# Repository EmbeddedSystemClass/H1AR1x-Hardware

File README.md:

# H1AR1x-Hardware
Hexabitz USB-B-to-UART Converter Module Hardware Design

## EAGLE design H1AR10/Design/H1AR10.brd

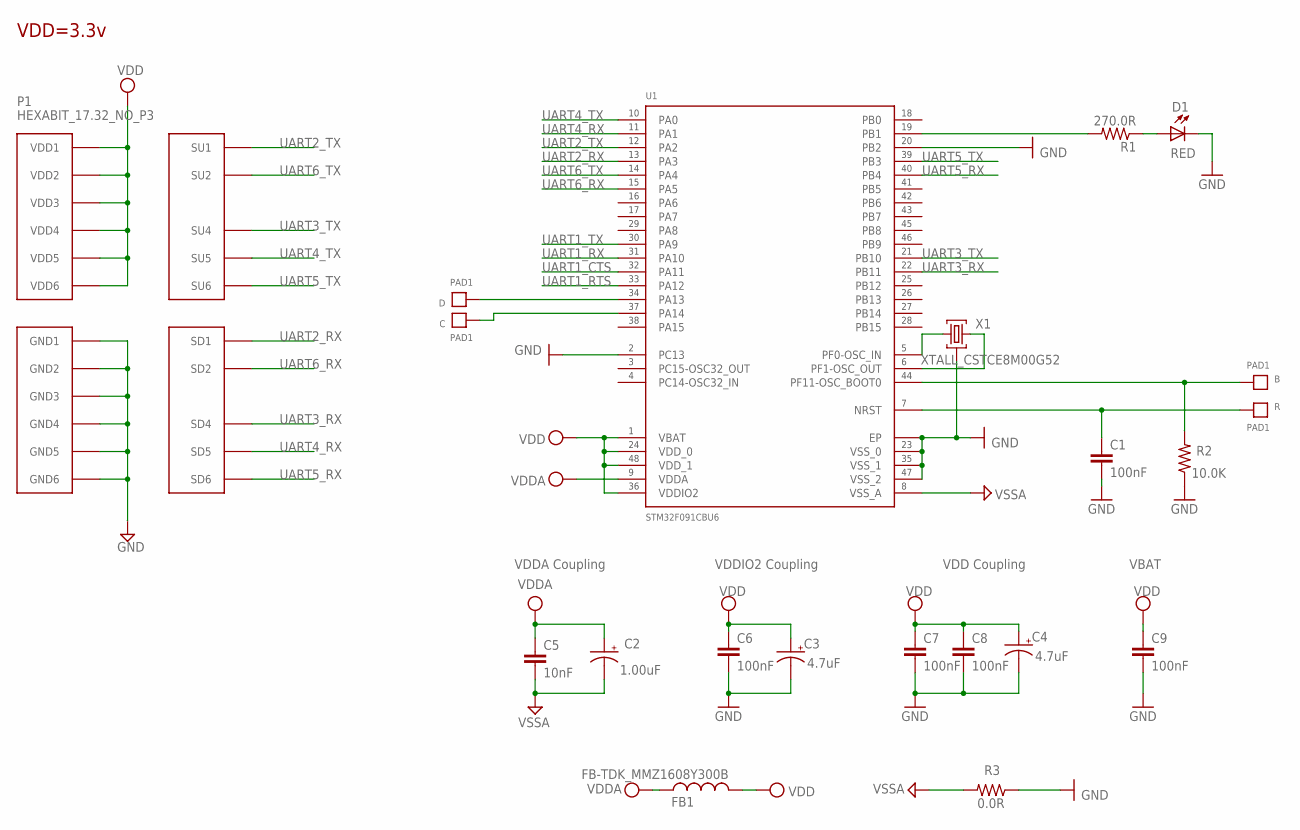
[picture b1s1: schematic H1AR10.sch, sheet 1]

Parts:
B: PAD1
C: PAD1
C1, C6, C7, C8, C9: 100nF; C-0603; TOLERANCE 10%; VOLTAGE_RATING 16V; MPN 0603YC104K4T2A
C2: 1.00uF; C-0805-POL; TOLERANCE 20%; VOLTAGE_RATING 16V; MPN TAJR105M016RNJ
C3, C4: 4.7uF; C-0805-POL; TOLERANCE 20%; VOLTAGE_RATING 10V; MPN 10TPU4R7MSI
C5: 10nF; C-0603; TOLERANCE 10%; VOLTAGE_RATING 16V; MPN 0603YC103KAT4A
D: PAD1
D1: RED; VLMS1300-GS08; MPN VLMS1300-GS08
FB1: FB-TDK_MMZ1608Y300B; MPN MMZ1608Y300B
P1: HEXABIT_17.32_NO_P3
R: PAD1
R1: 270.0R; R-0603; TOLERANCE 5%; MPN ERJ-3GEYJ271V
R2: 10.0K; R-0603; TOLERANCE 5%; MPN CRCW060310K0JNEB
R3: 0.0R; R-0603; MPN CRCW06030000Z0EAHP
U1: STM32F091CBU6
X1: XTALL_CSTCE8M00G52

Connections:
B1: B.P$1, B.P$2, R2.2, U1.P$44 (PF11-OSC_BOOT0)
GND: C1.2, C3.2 (-), C4.2 (-), C6.2, C7.2, C8.2, C9.2, D1.C, P1.PAD_PD7 (GND1), P1.PAD_PD8 (GND2), P1.PAD_PD9 (GND3), P1.PAD_PD10 (GND4), P1.PAD_PD11 (GND5), P1.PAD_PD12 (GND6), R2.1, R3.1, U1.EP, U1.P$2 (PC13), U1.P$20 (PB2), U1.P$23 (VSS_0), U1.P$35 (VSS_1), U1.P$47 (VSS_2), X1.P$2 (2); also elsewhere on the board
unnamed: U1.P$5 (PF0-OSC_IN), X1.P$1 (1)
unnamed: U1.P$6 (PF1-OSC_OUT), X1.P$3 (3)
unnamed: D.P$1, D.P$2, U1.P$34 (PA13)
unnamed: C.P$1, C.P$2, U1.P$37 (PA14)
unnamed: D1.A, R1.1
unnamed: R1.2, U1.P$19 (PB1)
R1: C1.1, R.P$1, R.P$2, U1.P$7 (NRST)
UART1_CTS: U1.P$32 (PA11); also elsewhere on the board
UART1_RTS: U1.P$33 (PA12); also elsewhere on the board
UART1_RX: U1.P$31 (PA10); also elsewhere on the board
UART1_TX: U1.P$30 (PA9); also elsewhere on the board
UART2_RX: P1.PAD_PD1 (SD1), U1.P$13 (PA3)
UART2_TX: P1.PAD_PU1 (SU1), U1.P$12 (PA2)
UART3_RX: P1.PAD_PD4 (SD4), U1.P$22 (PB11)
UART3_TX: P1.PAD_PU4 (SU4), U1.P$21 (PB10)
UART4_RX: P1.PAD_PD5 (SD5), U1.P$11 (PA1)
UART4_TX: P1.PAD_PU5 (SU5), U1.P$10 (PA0)
UART5_RX: P1.PAD_PD6 (SD6), U1.P$40 (PB4)
UART5_TX: P1.PAD_PU6 (SU6), U1.P$39 (PB3)
UART6_RX: P1.PAD_PD2 (SD2), U1.P$15 (PA5)
UART6_TX: P1.PAD_PU2 (SU2), U1.P$14 (PA4)
VDD: C3.1 (+), C4.1 (+), C6.1, C7.1, C8.1, C9.1, FB1.2, P1.PAD_PU7 (VDD1), P1.PAD_PU8 (VDD2), P1.PAD_PU9 (VDD3), P1.PAD_PU10 (VDD4), P1.PAD_PU11 (VDD5), P1.PAD_PU12 (VDD6), U1.P$1 (VBAT), U1.P$24 (VDD_0), U1.P$36 (VDDIO2), U1.P$48 (VDD_1); also elsewhere on the board
VDDA: C2.1 (+), C5.1, FB1.1, U1.P$9 (VDDA)
VSSA: C2.2 (-), C5.2, R3.2, U1.P$8 (VSS_A)

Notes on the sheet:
VDDA Coupling
VDDIO2 Coupling
VDD Coupling
VBAT
VDD=3.3v

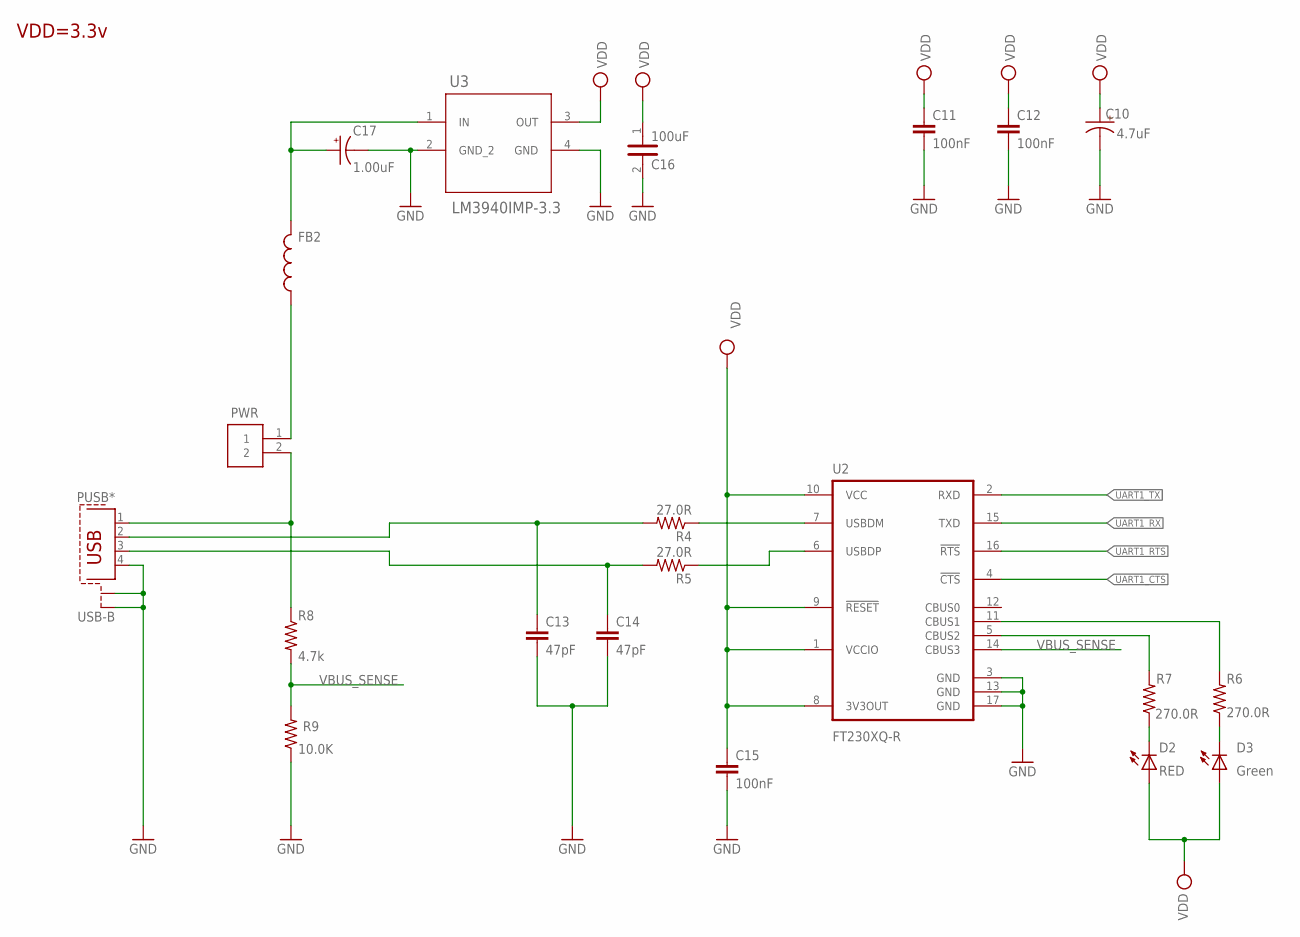
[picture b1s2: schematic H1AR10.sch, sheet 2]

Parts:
C10: 4.7uF; C-0805-POL; TOLERANCE 20%; VOLTAGE_RATING 10V; MPN 10TPU4R7MSI
C11, C12, C15: 100nF; C-0603; TOLERANCE 10%; VOLTAGE_RATING 16V; MPN 0603YC104K4T2A
C13, C14: 47pF; C-0603; TOLERANCE 5%; VOLTAGE_RATING 50; MPN AVX
C16: 100uF; C-3225; TOLERANCE 20%; VOLTAGE 6.3V; MPN C3225X5R0J107M250AC
C17: 1.00uF; C-0805-POL; TOLERANCE 20%; VOLTAGE_RATING 16V; MPN TAJR105M016RNJ
D2: RED; VLMS1300-GS08; MPN VLMS1300-GS08
D3: Green; VLMS1300-GS08; MPN VLMTG1300-GS08
FB2: FB-TDK_MMZ1608Y300B; MPN MMZ1608Y300B
PUSB*: USB-B; PN61729-S
PWR: 3-644456-2; TE_3-644456-2
R4, R5: 27.0R; R-0603; TOLERANCE 1%; MPN CRCW060327R0FKEA
R6, R7: 270.0R; R-0603; TOLERANCE 5%; MPN ERJ-3GEYJ271V
R8: 4.7k; R-0603; TOLERANCE 1%; MPN CRCW06034K70FKEA
R9: 10.0K; R-0603; TOLERANCE 5%; MPN CRCW060310K0JNEB
U2: FT230XQ-R; QFN16
U3: LM3940IMP-3.3; SOT230P696X180-4N

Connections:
GND: C10.2 (-), C11.2, C12.2, C13.2, C14.2, C15.2, C16.2, C17.2 (-), PUSB*.4, PUSB*.S1, PUSB*.S2, R9.1, U2.3 (GND), U2.13 (GND), U2.17 (GND), U3.2 (GND_2), U3.4 (GND); also elsewhere on the board
unnamed: D3.C, R6.1
unnamed: R7.2, U2.5 (CBUS2)
unnamed: D2.C, R7.1
unnamed: R6.2, U2.11 (CBUS1)
unnamed: R4.1, U2.7 (USBDM)
unnamed: R5.1, U2.6 (USBDP)
unnamed: C14.1, PUSB*.3, R5.2
unnamed: C13.1, PUSB*.2, R4.2
unnamed: FB2.1, PWR.1
unnamed: C17.1 (+), FB2.2, U3.1 (IN)
unnamed: PUSB*.1, PWR.2, R8.1
UART1_CTS: U2.4 (!CTS!); also elsewhere on the board
UART1_RTS: U2.16 (!RTS!); also elsewhere on the board
UART1_RX: U2.15 (TXD); also elsewhere on the board
UART1_TX: U2.2 (RXD); also elsewhere on the board
VBUS_SENSE: R8.2, R9.2, U2.14 (CBUS3)
VDD: C10.1 (+), C11.1, C12.1, C15.1, C16.1, D2.A, D3.A, U2.1 (VCCIO), U2.8 (3V3OUT), U2.9 (!RESET!), U2.10 (VCC), U3.3 (OUT); also elsewhere on the board

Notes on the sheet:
VDD=3.3v

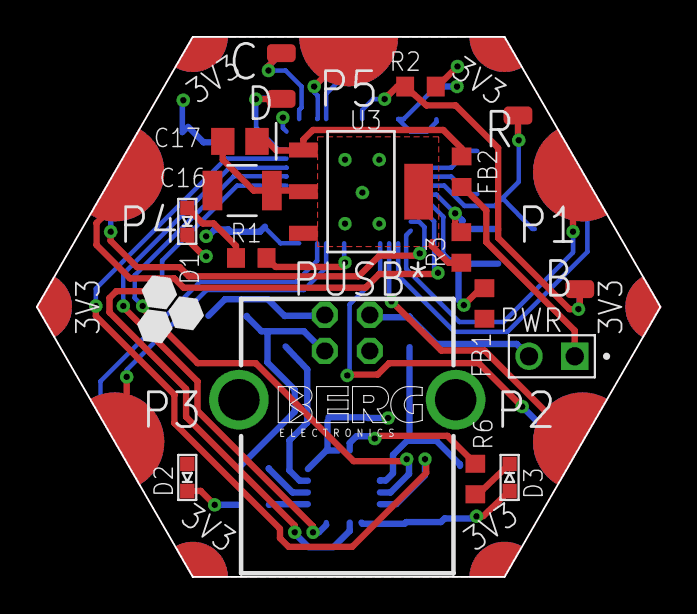
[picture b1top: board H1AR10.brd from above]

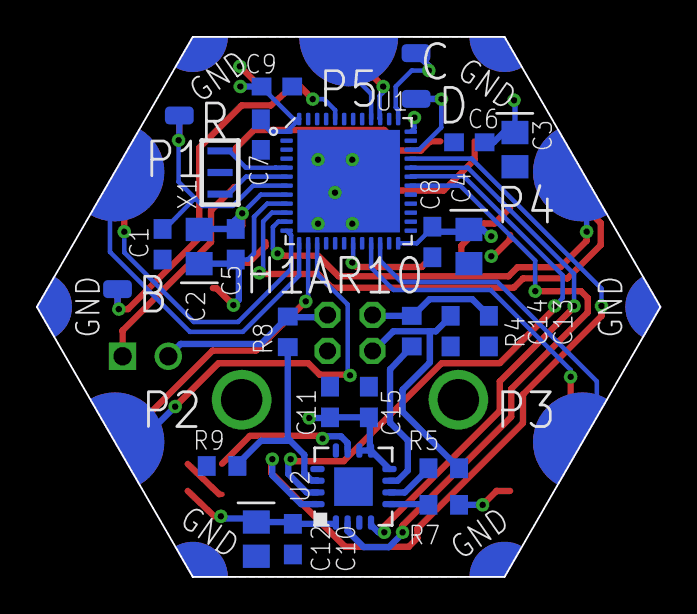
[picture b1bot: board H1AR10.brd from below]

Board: 2 copper layers, 34.6 x 30.0 mm, 42 parts (24 on the bottom side), 38 nets.

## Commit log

2020-03-01 Add template files
2020-03-08 complete UNchecked H1AR1
2020-03-09 Remove temp files
2020-03-15 final un-checked
2020-03-17 rotate "C" & "D" pads 90 degrees chage X2 (label) to PUSB* change the led pin to (PB1) pin make "R" pad away enough form "B" pad fix some clearnce issues
2020-03-24 no message
2020-03-24 USB_B hardware
